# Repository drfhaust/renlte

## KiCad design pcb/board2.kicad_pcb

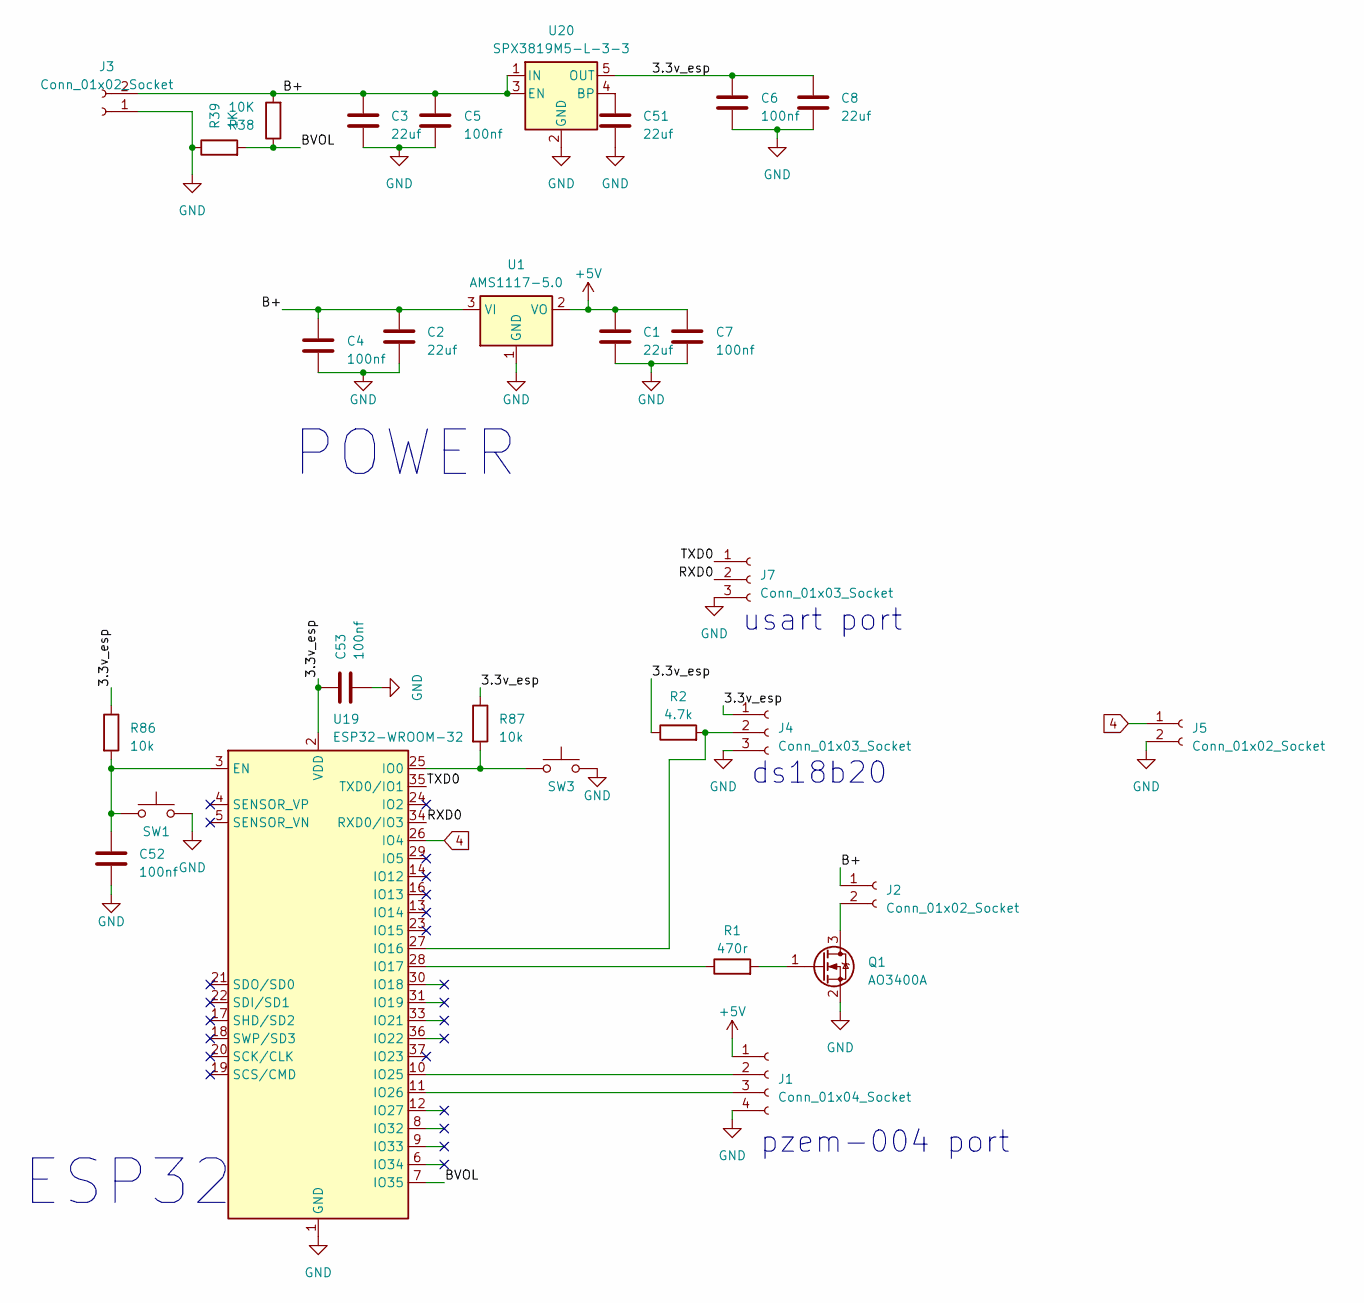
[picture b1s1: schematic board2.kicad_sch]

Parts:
C1, C2, C3, C8, C51: 22uf; C_0603_1608Metric
C4, C5, C6, C7, C52, C53: 100nf; C_0603_1608Metric
J1: Conn_01x04_Socket; JST_XA_B04B-XASK-1_1x04_P2.50mm_Vertical
J2, J3, J5: Conn_01x02_Socket; JST_XA_B02B-XASK-1_1x02_P2.50mm_Vertical
J4, J7: Conn_01x03_Socket; JST_XA_B03B-XASK-1_1x03_P2.50mm_Vertical
Q1: AO3400A; SOT-23
R1: 470r; R_0603_1608Metric
R2: 4.7k; R_0603_1608Metric
R38: 10K; R_0603_1608Metric
R39: 1K; R_0603_1608Metric
R86, R87: 10k; R_0603_1608Metric
SW1, SW3: TS-1101-B-W; Switch_Tactile_XKB-CONNECTIVITY_TS-1101-B-W; MPN TS-1101-B-W; LCSC PN C500065
U1: AMS1117-5.0; SOT-223-3_TabPin2
U19: ESP32-WROOM-32
U20: SPX3819M5-L-3-3; SOT-23-5

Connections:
4: J5.1, U19.26 (IO4)
+5V: C1.2, C7.2, J1.1, U1.2 (VO)
/3.3v_esp: C6.2, C8.2, C53.1, J4.1, R2.1, R86.1, R87.1, U19.2 (VDD), U20.5 (OUT)
/B+: C2.2, C3.2, C4.2, C5.2, J2.1, J3.2, R38.2, U1.3 (VI), U20.1 (IN), U20.3 (EN)
/BVOL: R38.1, R39.2, U19.7 (IO35)
/RXD0: J7.2, U19.34 (RXD0/IO3)
/TXD0: J7.1, U19.35 (TXD0/IO1)
GND: C1.1, C2.1, C3.1, C4.1, C5.1, C6.1, C7.1, C8.1, C51.1, C52.2, C53.2, J1.4, J3.1, J4.3, J5.2, J7.3, Q1.2 (S), R39.1, SW1.2, SW3.2, U1.1 (GND), U19.1 (GND), U19.15 (GND), U19.38 (GND), U19.39 (GND), U20.2 (GND)
unnamed: J1.2, U19.10 (IO25)
unnamed: J1.3, U19.11 (IO26)
unnamed: J2.2, Q1.3 (D)
unnamed: J4.2, R2.2, U19.27 (IO16)
unnamed: Q1.1 (G), R1.2
unnamed: C52.1, R86.2, SW1.1, U19.3 (EN)
unnamed: R87.2, SW3.1, U19.25 (IO0)
unnamed: R1.1, U19.28 (IO17)
unnamed: C51.2, U20.4 (BP)

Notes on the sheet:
ESP32
ds18b20
usart port
POWER
pzem-004 port

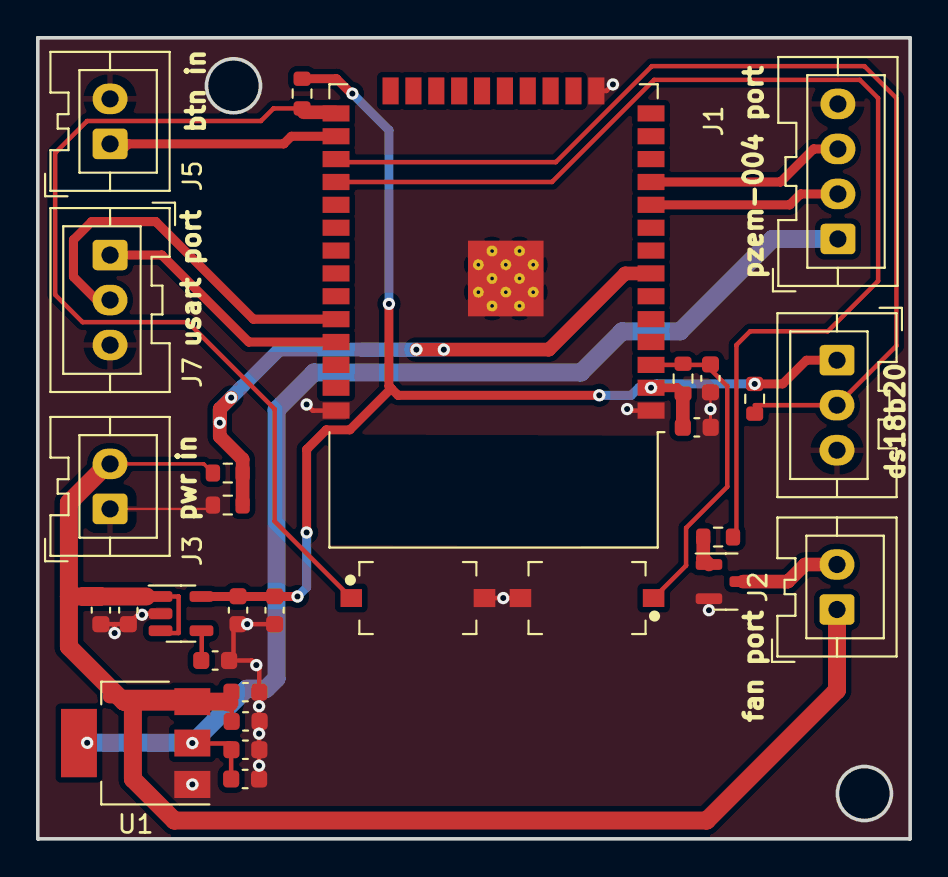
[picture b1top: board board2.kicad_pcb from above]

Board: 2 copper layers, 48.5 x 44.5 mm, 29 parts (0 on the bottom side), 17 nets.

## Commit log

2023-12-19 pcb done
2023-12-19 folders
2023-12-19 changed to 2 layers
2024-03-27 CODE
